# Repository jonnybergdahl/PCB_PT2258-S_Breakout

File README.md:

# Audio_PT2258-S_Breakout

This is a breakout board for the Princeton Technoloy PT2258-S chip. 

According to the manufacturer:
> PT2258 is a 6-Channel Electronic Volume Controller IC utilizing CMOS Technology specially designed
for the new generation of AV Multi-Channel Audio System. PT2258 provides an I2
C Control Interface,
an attenuation range of 0 to -79dB at 1dB/step, low noise, and high channel separation.

## I2C pins

Name | Description
---- | ----
GND | Ground
SCL | Serial clock line
SDA | Serial data line

## Inputs
Name | Description
---- | ----
1 | Input 1
2 | Input 2
3 | Input 3
4 | Input 4
5 | Input 5
6 | Input 6
GND | Ground (6 of them)

## Outputs
Name | Description
---- | ----
1 | Output 1
2 | Output 2
3 | Output 3
4 | Output 4
5 | Output 5
6 | Output 6
GND | Ground (6 of them)

## Power
Name | Description
---- | ----
VCC | 5-9V power
GND | Ground

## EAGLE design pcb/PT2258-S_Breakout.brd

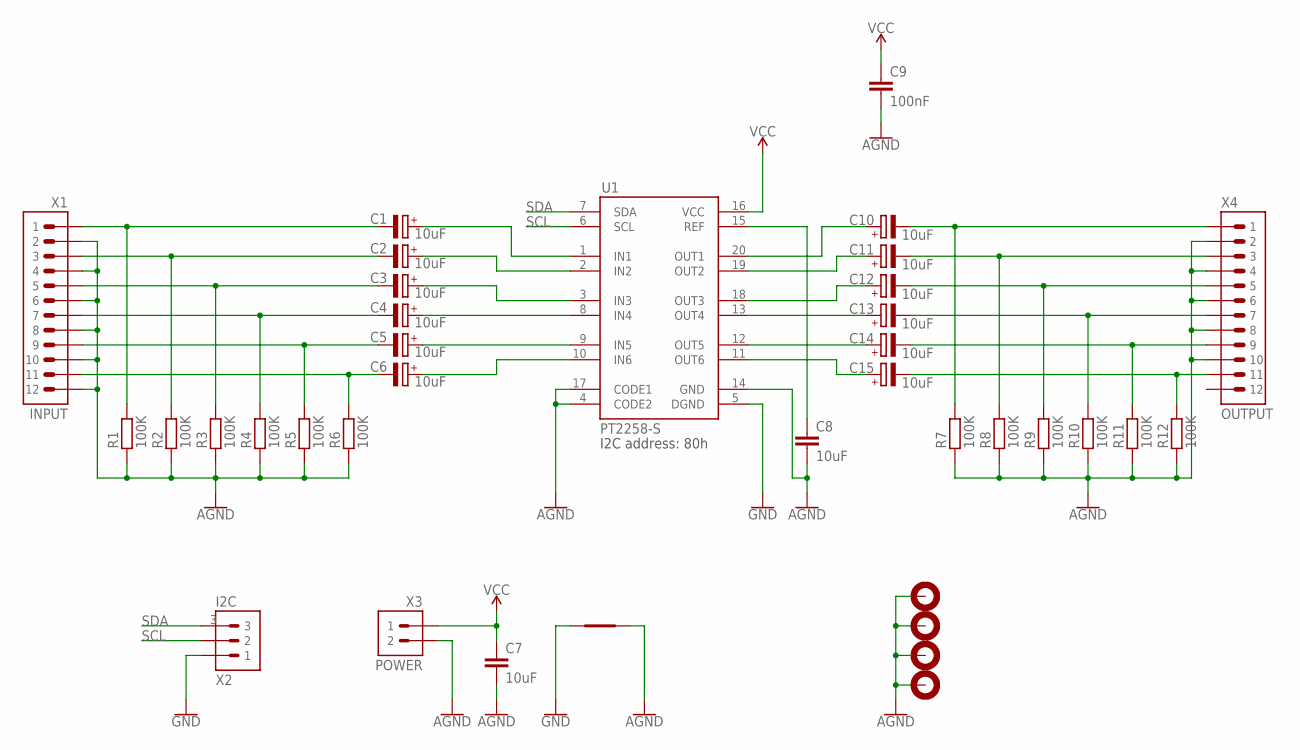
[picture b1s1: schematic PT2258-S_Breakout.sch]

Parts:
C1, C2, C3, C4, C5, C6, C10, C11, C12, C13, C14, C15: 10uF; ROQANG-RVT0405
C7, C8: 10uF; C0603
C9: 100nF; C0603
H1, H2, H3, H4: MOUNTHOLE-PAD3.2; 3.2-PAD
R1, R2, R3, R4, R5, R6, R7, R8, R9, R10, R11, R12: 100K; R0603
SH1: SHORT-SMD-06096
U1: PT2258-S; SOP-20-300
X1: INPUT; 1X12-2.54
X2: I2C; 1X03P-2.54
X3: POWER; 1X02P-2.54
X4: OUTPUT; 1X12-2.54

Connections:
AGND: C7.2, C8.2, C9.2, H1.B3,2, H2.B3,2, H3.B3,2, H4.B3,2, R1.1, R2.1, R3.1, R4.1, R5.1, R6.1, R7.1, R8.1, R9.1, R10.1, R11.1, R12.1, SH1.2, U1.4 (CODE2), U1.14 (GND), U1.17 (CODE1), X1.2, X1.4, X1.6, X1.8, X1.10, X1.12, X3.2, X4.2, X4.4, X4.6, X4.8, X4.10
GND: SH1.1, U1.5 (DGND), X2.1
unnamed: C10.-, R7.2, X4.1
unnamed: C11.-, R8.2, X4.3
unnamed: C12.-, R9.2, X4.5
unnamed: C13.-, R10.2, X4.7
unnamed: C14.-, R11.2, X4.9
unnamed: C15.-, R12.2, X4.11
unnamed: C4.+, U1.8 (IN4)
unnamed: C1.+, U1.1 (IN1)
unnamed: C15.+, U1.11 (OUT6)
unnamed: C14.+, U1.12 (OUT5)
unnamed: C13.+, U1.13 (OUT4)
unnamed: C12.+, U1.18 (OUT3)
unnamed: C11.+, U1.19 (OUT2)
unnamed: C10.+, U1.20 (OUT1)
unnamed: C8.1, U1.15 (REF)
unnamed: C2.+, U1.2 (IN2)
unnamed: C3.+, U1.3 (IN3)
unnamed: C5.+, U1.9 (IN5)
unnamed: C6.+, U1.10 (IN6)
unnamed: C1.-, R1.2, X1.1
unnamed: C2.-, R2.2, X1.3
unnamed: C3.-, R3.2, X1.5
unnamed: C4.-, R4.2, X1.7
unnamed: C5.-, R5.2, X1.9
unnamed: C6.-, R6.2, X1.11
SCL: U1.6 (SCL), X2.2
SDA: U1.7 (SDA), X2.3
VCC: C7.1, C9.1, U1.16 (VCC), X3.1

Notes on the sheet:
I2C address: 80h

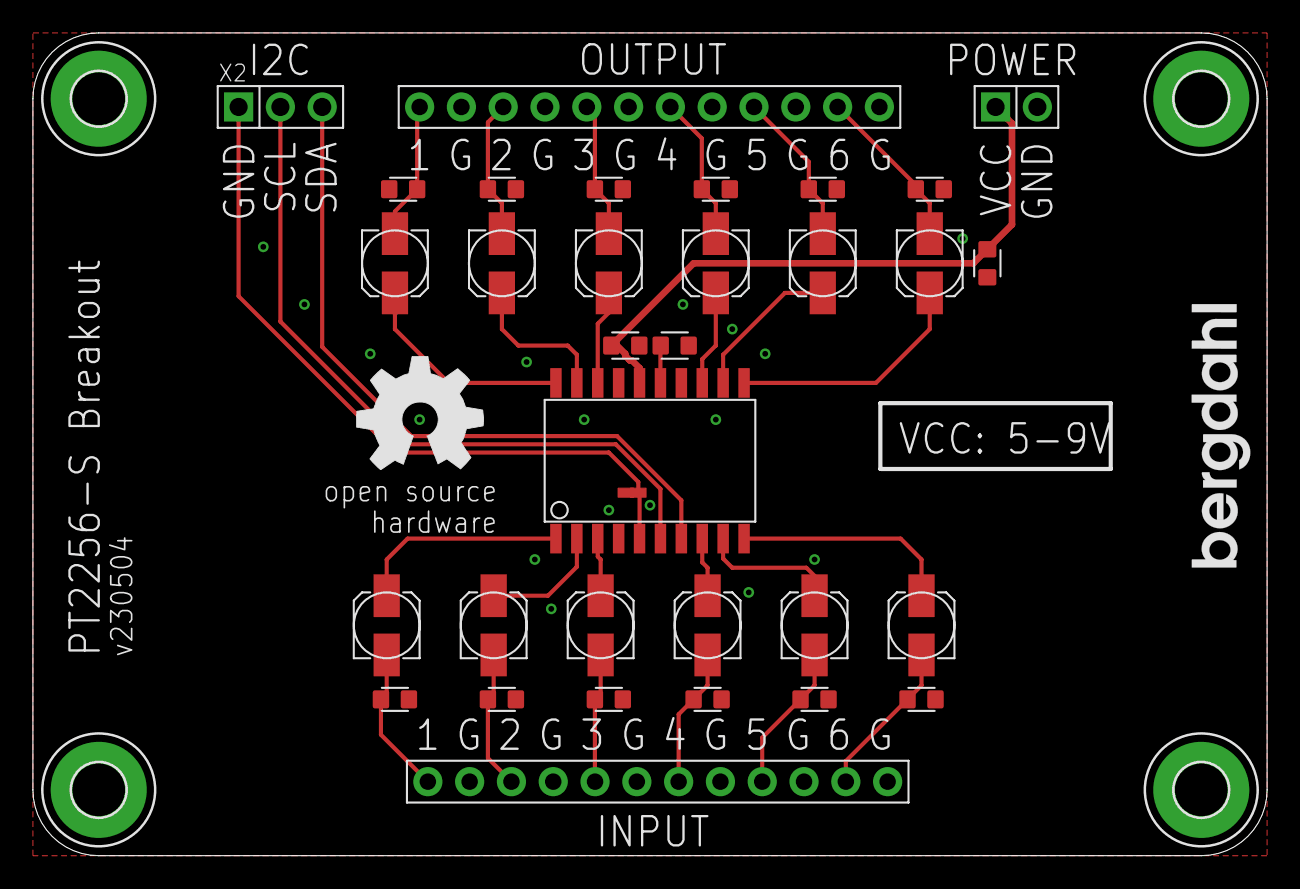
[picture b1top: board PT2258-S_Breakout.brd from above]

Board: 2 copper layers, 75.0 x 50.0 mm, 41 parts (0 on the bottom side), 30 nets.

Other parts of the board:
U$1: BERGDAHL-20MM-BPLACE
U$2: OSHW-8MM-BPLACE
U$3: BERGDAHL-20MM-TPLACE
U$5: OSHW-8MM-TPLACE

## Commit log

2023-04-30 Final version
2023-04-30 Update PDF
2023-06-04 Fix SOP-20-300 footprint
